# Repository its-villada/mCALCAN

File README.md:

# mCALCAN
Satélite CANSAT del instituto técnico salesiano Villada. 
Este desarrollo responde a la iniciativa conjunta entre la Comisión Nacional de Actividades Espaciales (CONAE) y el Ministerio de Ciencia, Tecnología e Innovación (MinCyT) tiene como objetivo principal acercar la
ciencia y la tecnología a jóvenes en edad escolar, mediante la participación en la Convocatoria CANSAT Argentina.

## Objetivos
### Misión Primaria
Consiste en el sensado de presión y temperatura y la transmisión de esos datos a la estación terrena,al menos una vez por segundo. Mediante estos dos parámetros calcularemos la altitud, ya que tanto presión como temperatura varían con la altitud.
Para el cálculo de la altura, nuestro CANSAT transmitirá los datos de temperatura y presión antes del despegue y de esa manera obtener los datos iniciales necesarios para el cálculo.
### Misión Secundaria
Aprovechando y como complemento de la misión primaria, la misión secundaria consiste en medir la atmósfera y sus condiciones, con el objetivo de armar un perfil de atmósfera que pueda ser implementado, más adelante, como parte del modelo meteorológico internacional para la generación de pronósticos o la calibración de radares meteorológicos. Esto significa, que se medirán parámetros ambientales de presión y temperatura (tomados en la misión primaria), a los que agregaremos
humedad relativa y porcentaje de CO2. Estos parámetros son medidos y correlacionados con las coordenadas (latitud, longitud y altitud) obtenidas por un módulo GPS.

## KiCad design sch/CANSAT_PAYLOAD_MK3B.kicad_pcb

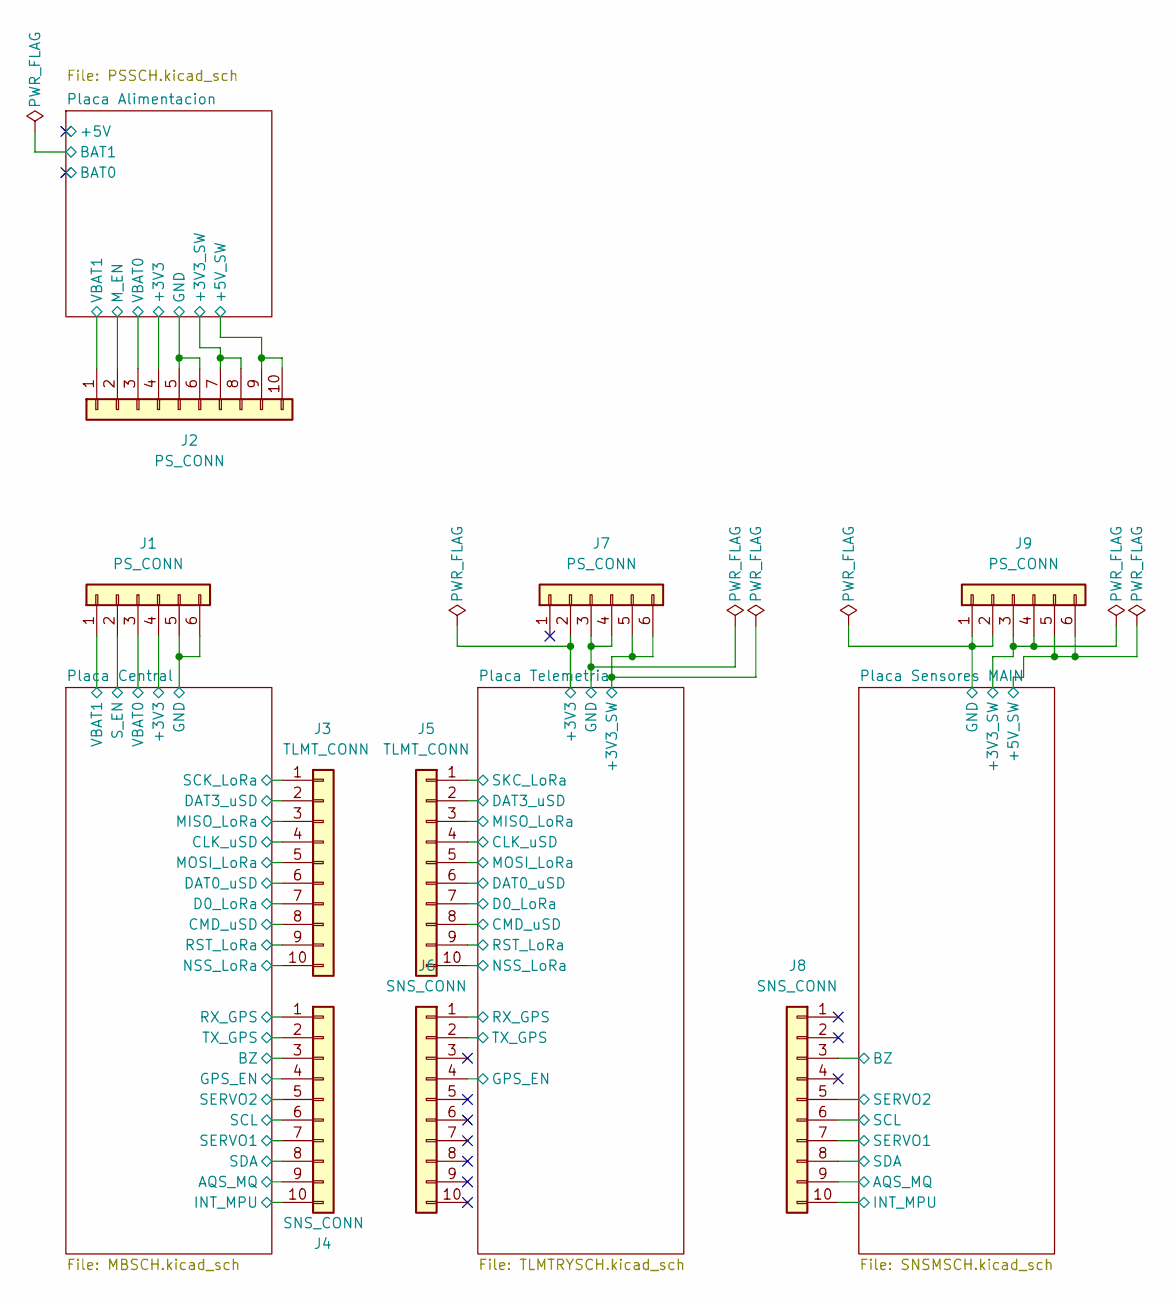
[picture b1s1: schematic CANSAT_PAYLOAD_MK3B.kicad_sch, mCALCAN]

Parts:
J1, J7, J9: PS_CONN; PCB_CONN_S
J2: PS_CONN; PCB_CONN
J3, J5: TLMT_CONN; PCB_CONN
J4, J6, J8: SNS_CONN; PCB_CONN

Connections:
/Placa Alimentacion/+3V3: J2.4; also elsewhere on the board
/Placa Alimentacion/+3V3_SW: J2.7, J2.8; also elsewhere on the board
/Placa Alimentacion/+5V_SW: J2.9, J2.10; also elsewhere on the board
/Placa Alimentacion/GND: J2.5, J2.6; also elsewhere on the board
/Placa Alimentacion/M_EN: J2.2; also elsewhere on the board
/Placa Alimentacion/VBAT0: J2.3; also elsewhere on the board
/Placa Alimentacion/VBAT1: J2.1; also elsewhere on the board
/Placa Central/+3V3: J1.4; also elsewhere on the board
/Placa Central/AQS_MQ: J4.9; also elsewhere on the board
/Placa Central/BZ: J4.3; also elsewhere on the board
/Placa Central/CLK_uSD: J3.4; also elsewhere on the board
/Placa Central/CMD_uSD: J3.8; also elsewhere on the board
/Placa Central/D0_LoRa: J3.7; also elsewhere on the board
/Placa Central/DAT0_uSD: J3.6; also elsewhere on the board
/Placa Central/DAT3_uSD: J3.2; also elsewhere on the board
/Placa Central/GND: J1.5, J1.6; also elsewhere on the board
/Placa Central/GPS_EN: J4.4; also elsewhere on the board
/Placa Central/INT_MPU: J4.10; also elsewhere on the board
/Placa Central/MISO_LoRa: J3.3; also elsewhere on the board
/Placa Central/MOSI_LoRa: J3.5; also elsewhere on the board
/Placa Central/NSS_LoRa: J3.10; also elsewhere on the board
/Placa Central/RST_LoRa: J3.9; also elsewhere on the board
/Placa Central/RX_GPS: J4.1; also elsewhere on the board
/Placa Central/SCK_LoRa: J3.1; also elsewhere on the board
/Placa Central/SCL: J4.6; also elsewhere on the board
/Placa Central/SDA: J4.8; also elsewhere on the board
/Placa Central/SERVO1: J4.7; also elsewhere on the board
/Placa Central/SERVO2: J4.5; also elsewhere on the board
/Placa Central/S_EN: J1.2; also elsewhere on the board
/Placa Central/TX_GPS: J4.2; also elsewhere on the board
/Placa Central/VBAT0: J1.3; also elsewhere on the board
/Placa Central/VBAT1: J1.1; also elsewhere on the board
/Placa Sensores MAIN/+3V3_SW: J9.3, J9.4; also elsewhere on the board
/Placa Sensores MAIN/+5V_SW: J9.5, J9.6; also elsewhere on the board
/Placa Sensores MAIN/AQS_MQ: J8.9; also elsewhere on the board
/Placa Sensores MAIN/BZ: J8.3; also elsewhere on the board
/Placa Sensores MAIN/GND: J9.1, J9.2; also elsewhere on the board
/Placa Sensores MAIN/INT_MPU: J8.10; also elsewhere on the board
/Placa Sensores MAIN/SCL: J8.6; also elsewhere on the board
/Placa Sensores MAIN/SDA: J8.8; also elsewhere on the board
/Placa Sensores MAIN/SERVO1: J8.7; also elsewhere on the board
/Placa Sensores MAIN/SERVO2: J8.5; also elsewhere on the board
/Placa Telemetria/+3V3: J7.2; also elsewhere on the board
/Placa Telemetria/+3V3_SW: J7.5, J7.6; also elsewhere on the board
/Placa Telemetria/CLK_uSD: J5.4; also elsewhere on the board
/Placa Telemetria/CMD_uSD: J5.8; also elsewhere on the board
/Placa Telemetria/D0_LoRa: J5.7; also elsewhere on the board
/Placa Telemetria/DAT0_uSD: J5.6; also elsewhere on the board
/Placa Telemetria/DAT3_uSD: J5.2; also elsewhere on the board
/Placa Telemetria/GND: J7.3, J7.4; also elsewhere on the board
/Placa Telemetria/GPS_EN: J6.4; also elsewhere on the board
/Placa Telemetria/MISO_LoRa: J5.3; also elsewhere on the board
/Placa Telemetria/MOSI_LoRa: J5.5; also elsewhere on the board
/Placa Telemetria/NSS_LoRa: J5.10; also elsewhere on the board
/Placa Telemetria/RST_LoRa: J5.9; also elsewhere on the board
/Placa Telemetria/RX_GPS: J6.1; also elsewhere on the board
/Placa Telemetria/SKC_LoRa: J5.1; also elsewhere on the board
/Placa Telemetria/TX_GPS: J6.2; also elsewhere on the board

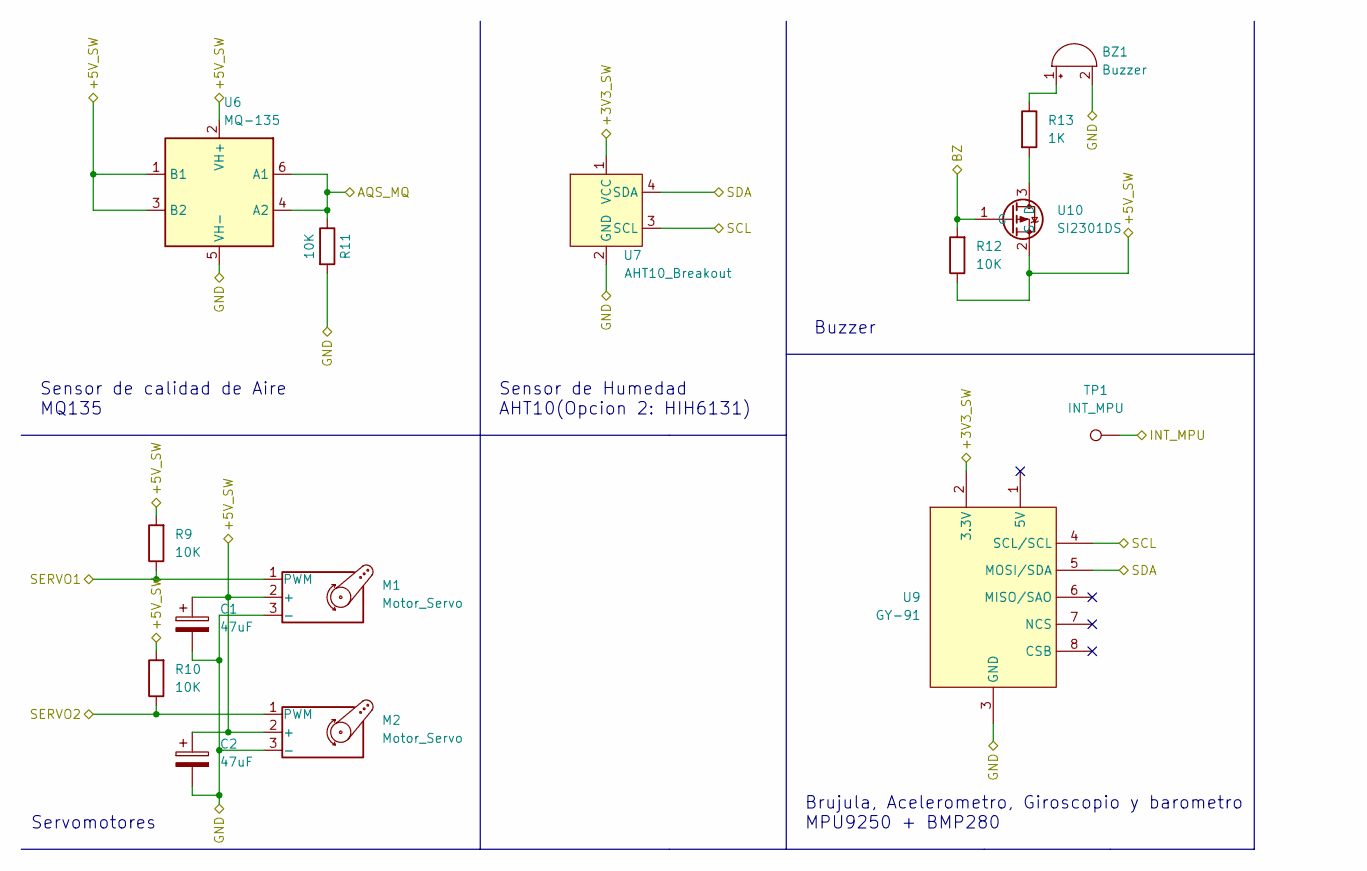
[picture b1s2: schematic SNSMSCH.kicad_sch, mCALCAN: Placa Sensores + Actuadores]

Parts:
BZ1: Buzzer; Buzzer_12x9.5RM7.6
C1, C2: 47uF; CP_Elec_4x5.3
M1, M2: Motor_Servo; PinHeader_1x03_P2.54mm_Vertical
R9, R10, R11, R12: 10K; R_0805_2012Metric_Pad1.20x1.40mm_HandSolder
R13: 1K; R_0805_2012Metric_Pad1.20x1.40mm_HandSolder
TP1: INT_MPU; TestPoint_THTPad_D1.5mm_Drill0.7mm
U6: MQ-135; MQ-6
U7: AHT10_Breakout
U9: GY-91; GY-91_Breakout
U10: SI2301DS; SOT-23

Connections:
/Placa Sensores MAIN/+3V3_SW: U7.1 (VCC), U9.2 (3.3V); also elsewhere on the board
/Placa Sensores MAIN/+5V_SW: C1.1, C2.1, M1.2 (+), M2.2 (+), R9.2, R10.2, R12.1, U6.1 (B1), U6.2 (VH+), U6.3 (B2), U10.2 (S); also elsewhere on the board
/Placa Sensores MAIN/AQS_MQ: R11.1, U6.4 (A2), U6.6 (A1); also elsewhere on the board
/Placa Sensores MAIN/BZ: R12.2, U10.1 (G); also elsewhere on the board
/Placa Sensores MAIN/GND: BZ1.2 (+), C1.2, C2.2, M1.3 (-), M2.3 (-), R11.2, U6.5 (VH-), U7.2 (GND), U9.3 (GND); also elsewhere on the board
/Placa Sensores MAIN/INT_MPU: TP1.1; also elsewhere on the board
/Placa Sensores MAIN/SCL: U7.3 (SCL), U9.4 (SCL/SCL); also elsewhere on the board
/Placa Sensores MAIN/SDA: U7.4 (SDA), U9.5 (MOSI/SDA); also elsewhere on the board
/Placa Sensores MAIN/SERVO1: M1.1 (PWM), R9.1; also elsewhere on the board
/Placa Sensores MAIN/SERVO2: M2.1 (PWM), R10.1; also elsewhere on the board
unnamed: BZ1.1 (-), R13.1
unnamed: R13.2, U10.3 (D)

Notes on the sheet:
Buzzer
Sensor de Humedad AHT10(Opcion 2: HIH6131)
Brujula, Acelerometro, Giroscopio y barometro MPU9250 + BMP280
Sensor de calidad de Aire MQ135
Servomotores

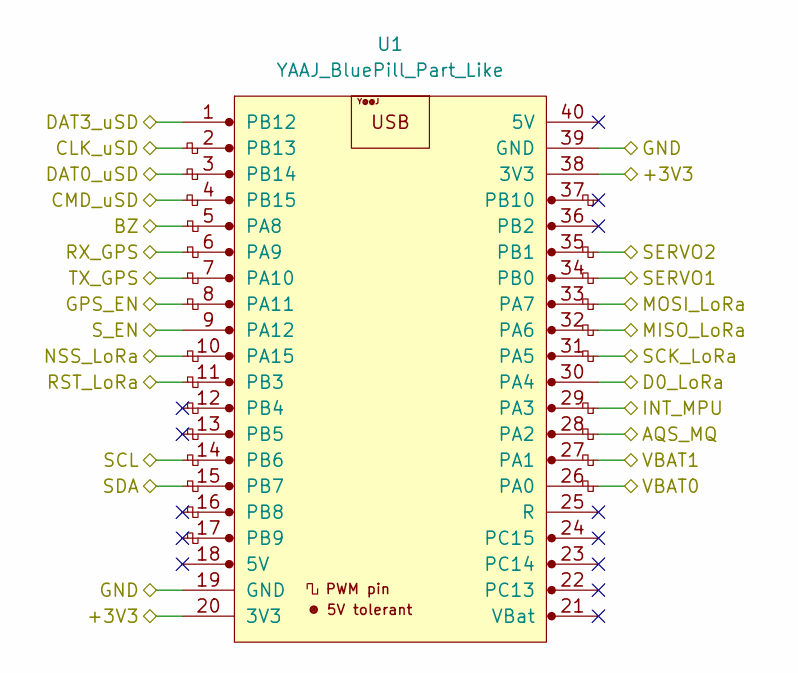
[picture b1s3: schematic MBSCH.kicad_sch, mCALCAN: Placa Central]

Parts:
U1: YAAJ_BluePill_Part_Like; YAAJ_BluePill_2

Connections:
/Placa Central/+3V3: U1.20 (3V3), U1.38 (3V3); also elsewhere on the board
/Placa Central/AQS_MQ: U1.28 (PA2); also elsewhere on the board
/Placa Central/BZ: U1.5 (PA8); also elsewhere on the board
/Placa Central/CLK_uSD: U1.2 (PB13); also elsewhere on the board
/Placa Central/CMD_uSD: U1.4 (PB15); also elsewhere on the board
/Placa Central/D0_LoRa: U1.30 (PA4); also elsewhere on the board
/Placa Central/DAT0_uSD: U1.3 (PB14); also elsewhere on the board
/Placa Central/DAT3_uSD: U1.1 (PB12); also elsewhere on the board
/Placa Central/GND: U1.19 (GND), U1.39 (GND); also elsewhere on the board
/Placa Central/GPS_EN: U1.8 (PA11); also elsewhere on the board
/Placa Central/INT_MPU: U1.29 (PA3); also elsewhere on the board
/Placa Central/MISO_LoRa: U1.32 (PA6); also elsewhere on the board
/Placa Central/MOSI_LoRa: U1.33 (PA7); also elsewhere on the board
/Placa Central/NSS_LoRa: U1.10 (PA15); also elsewhere on the board
/Placa Central/RST_LoRa: U1.11 (PB3); also elsewhere on the board
/Placa Central/RX_GPS: U1.6 (PA9); also elsewhere on the board
/Placa Central/SCK_LoRa: U1.31 (PA5); also elsewhere on the board
/Placa Central/SCL: U1.14 (PB6); also elsewhere on the board
/Placa Central/SDA: U1.15 (PB7); also elsewhere on the board
/Placa Central/SERVO1: U1.34 (PB0); also elsewhere on the board
/Placa Central/SERVO2: U1.35 (PB1); also elsewhere on the board
/Placa Central/S_EN: U1.9 (PA12); also elsewhere on the board
/Placa Central/TX_GPS: U1.7 (PA10); also elsewhere on the board
/Placa Central/VBAT0: U1.26 (PA0); also elsewhere on the board
/Placa Central/VBAT1: U1.27 (PA1); also elsewhere on the board

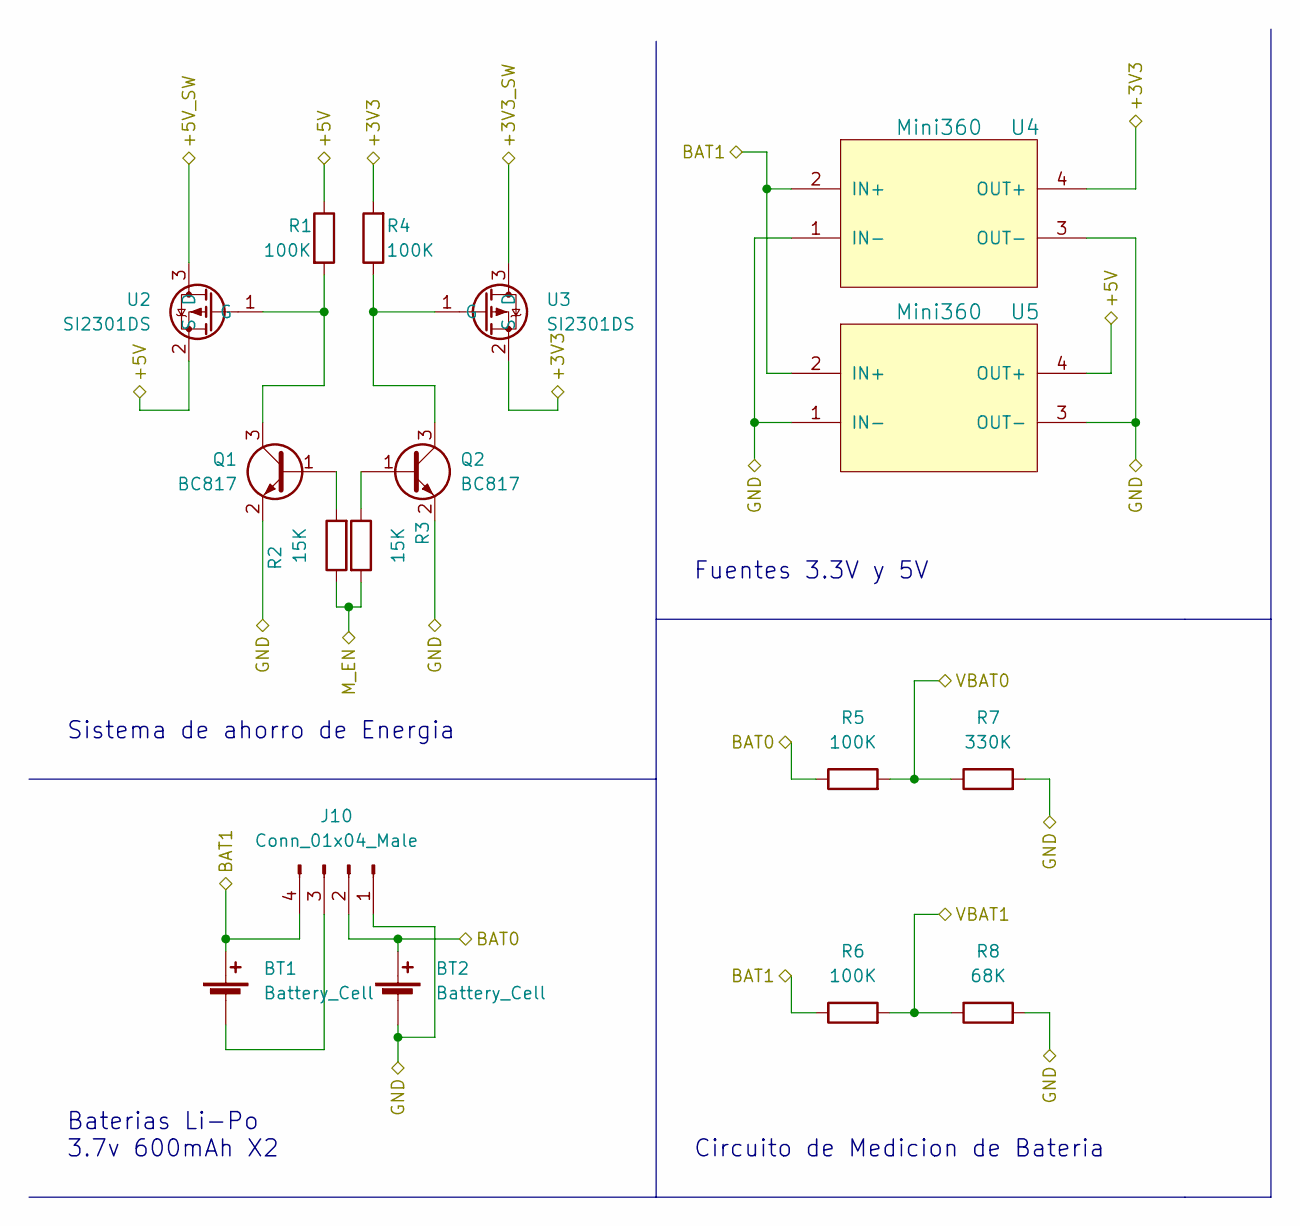
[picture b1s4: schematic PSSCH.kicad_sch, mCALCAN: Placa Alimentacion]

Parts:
BT1, BT2: Battery_Cell; Molex_Micro-Latch_53253-0270_1x02_P2.00mm_Vertical
J10: Conn_01x04_Male; PinHeader_1x04_P2.54mm_Vertical
Q1, Q2: BC817; SOT-23
R1, R4, R5, R6: 100K; R_0805_2012Metric_Pad1.20x1.40mm_HandSolder
R2, R3: 15K; R_0805_2012Metric_Pad1.20x1.40mm_HandSolder
R7: 330K; R_0805_2012Metric_Pad1.20x1.40mm_HandSolder
R8: 68K; R_0805_2012Metric_Pad1.20x1.40mm_HandSolder
U2, U3: SI2301DS; SOT-23
U4, U5: Mini360; Mini360_step-down

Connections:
/Placa Alimentacion/+3V3: R4.2, U3.2 (S), U4.4 (OUT+); also elsewhere on the board
/Placa Alimentacion/+3V3_SW: U3.3 (D); also elsewhere on the board
/Placa Alimentacion/+5V: R1.1, U2.2 (S), U5.4 (OUT+)
/Placa Alimentacion/+5V_SW: U2.3 (D); also elsewhere on the board
/Placa Alimentacion/BAT0: BT2.1 (+), J10.2, R5.1
/Placa Alimentacion/BAT1: BT1.1 (+), J10.4, R6.1, U4.2 (IN+), U5.2 (IN+)
/Placa Alimentacion/GND: BT2.2 (-), J10.1, Q1.2 (E), Q2.2 (E), R7.2, R8.2, U4.1 (IN-), U4.3 (OUT-), U5.1 (IN-), U5.3 (OUT-); also elsewhere on the board
/Placa Alimentacion/M_EN: R2.1, R3.2; also elsewhere on the board
/Placa Alimentacion/VBAT0: R5.2, R7.1; also elsewhere on the board
/Placa Alimentacion/VBAT1: R6.2, R8.1; also elsewhere on the board
unnamed: BT1.2 (-), J10.3
unnamed: Q1.1 (B), R2.2
unnamed: Q1.3 (C), R1.2, U2.1 (G)
unnamed: Q2.1 (B), R3.1
unnamed: Q2.3 (C), R4.1, U3.1 (G)

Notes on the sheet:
Baterias Li-Po 3.7v 600mAh X2
Sistema de ahorro de Energia
Fuentes 3.3V y 5V
Circuito de Medicion de Bateria

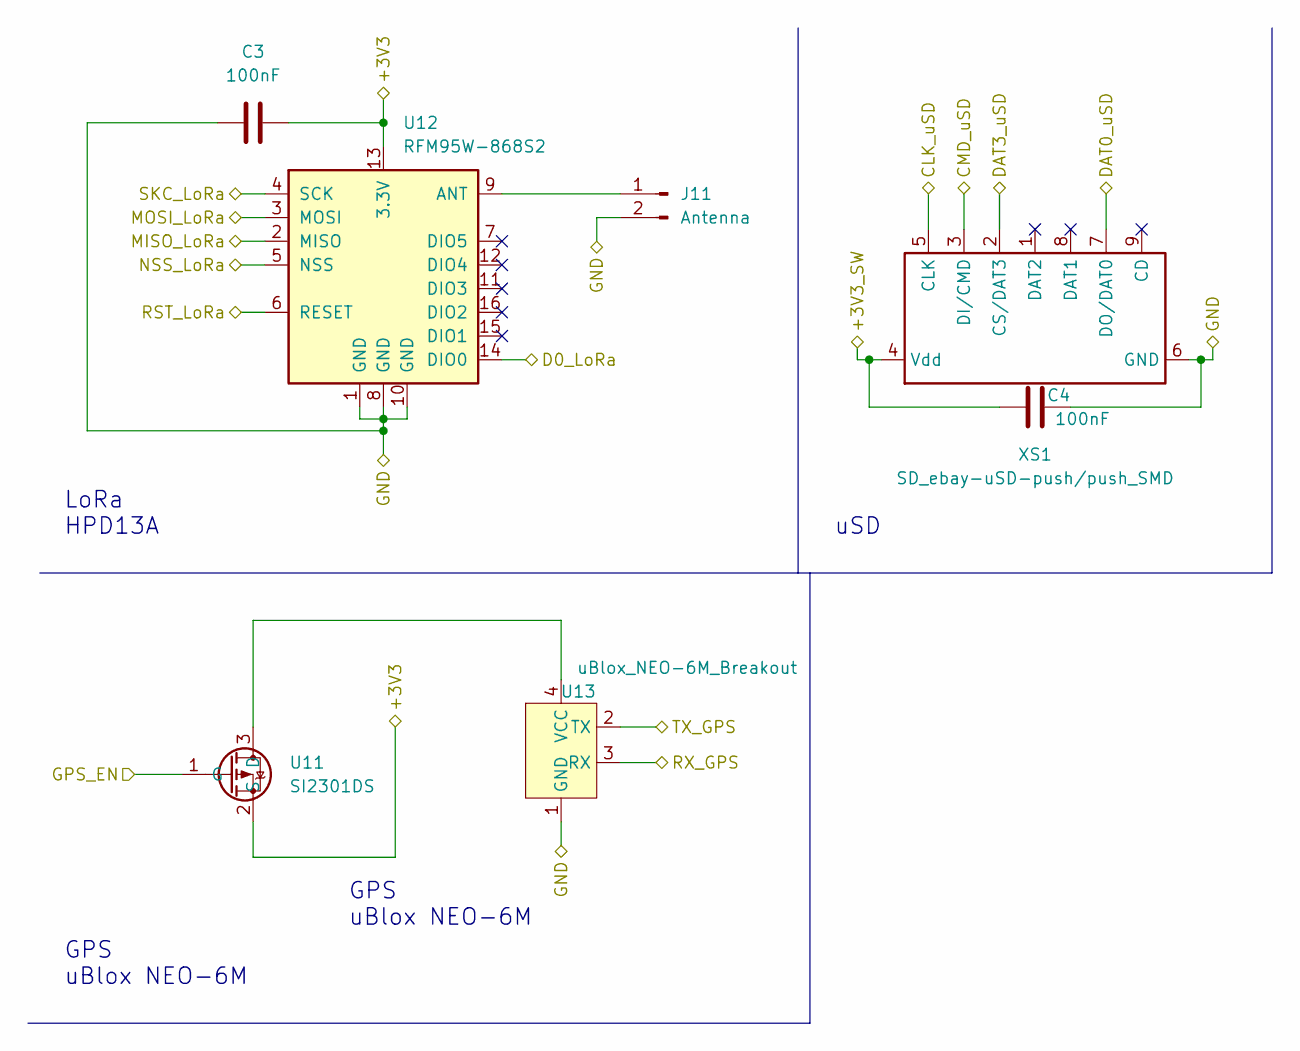
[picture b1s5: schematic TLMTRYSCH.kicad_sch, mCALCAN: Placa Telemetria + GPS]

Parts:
C3, C4: 100nF; C_0805_2012Metric_Pad1.18x1.45mm_HandSolder
J11: Antenna; U.FL_Molex_MCRF_73412-0110_Vertical
U11: SI2301DS; SOT-23
U12: RFM95W-868S2; HOPERF_RFM9XW_SMD
U13: uBlox_NEO-6M_Breakout; uBlox-NEO-6M_Breakout
XS1: SD_ebay-uSD-push/push_SMD; Conn_uSDcard

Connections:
/Placa Telemetria/+3V3: C3.2, U11.2 (S), U12.13 (3.3V); also elsewhere on the board
/Placa Telemetria/+3V3_SW: C4.1, XS1.4 (Vdd); also elsewhere on the board
/Placa Telemetria/CLK_uSD: XS1.5 (CLK); also elsewhere on the board
/Placa Telemetria/CMD_uSD: XS1.3 (DI/CMD); also elsewhere on the board
/Placa Telemetria/D0_LoRa: U12.14 (DIO0); also elsewhere on the board
/Placa Telemetria/DAT0_uSD: XS1.7 (DO/DAT0); also elsewhere on the board
/Placa Telemetria/DAT3_uSD: XS1.2 (CS/DAT3); also elsewhere on the board
/Placa Telemetria/GND: C3.1, C4.2, J11.2, U12.1 (GND), U12.8 (GND), U12.10 (GND), U13.1 (GND), XS1.6 (GND); also elsewhere on the board
/Placa Telemetria/GPS_EN: U11.1 (G); also elsewhere on the board
/Placa Telemetria/MISO_LoRa: U12.2 (MISO); also elsewhere on the board
/Placa Telemetria/MOSI_LoRa: U12.3 (MOSI); also elsewhere on the board
/Placa Telemetria/NSS_LoRa: U12.5 (NSS); also elsewhere on the board
/Placa Telemetria/RST_LoRa: U12.6 (RESET); also elsewhere on the board
/Placa Telemetria/RX_GPS: U13.3 (RX); also elsewhere on the board
/Placa Telemetria/SKC_LoRa: U12.4 (SCK); also elsewhere on the board
/Placa Telemetria/TX_GPS: U13.2 (TX); also elsewhere on the board
unnamed: J11.1, U12.9 (ANT)
unnamed: U11.3 (D), U13.4 (VCC)

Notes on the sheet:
GPS uBlox NEO-6M
LoRa HPD13A
uSD

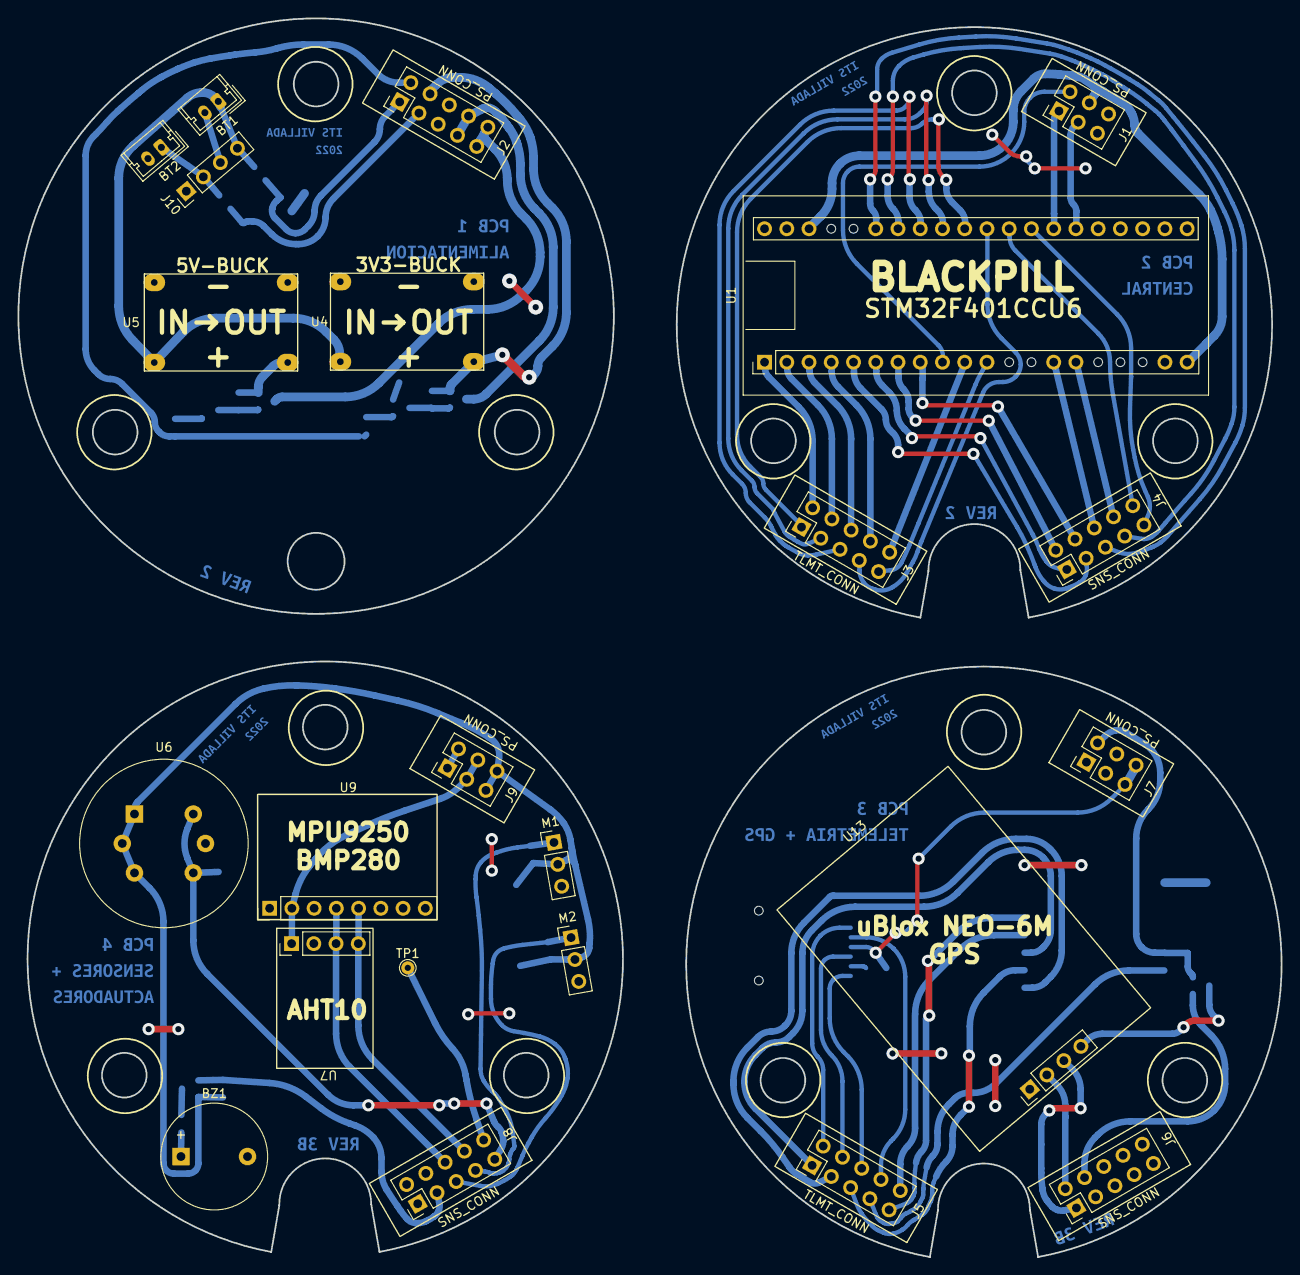
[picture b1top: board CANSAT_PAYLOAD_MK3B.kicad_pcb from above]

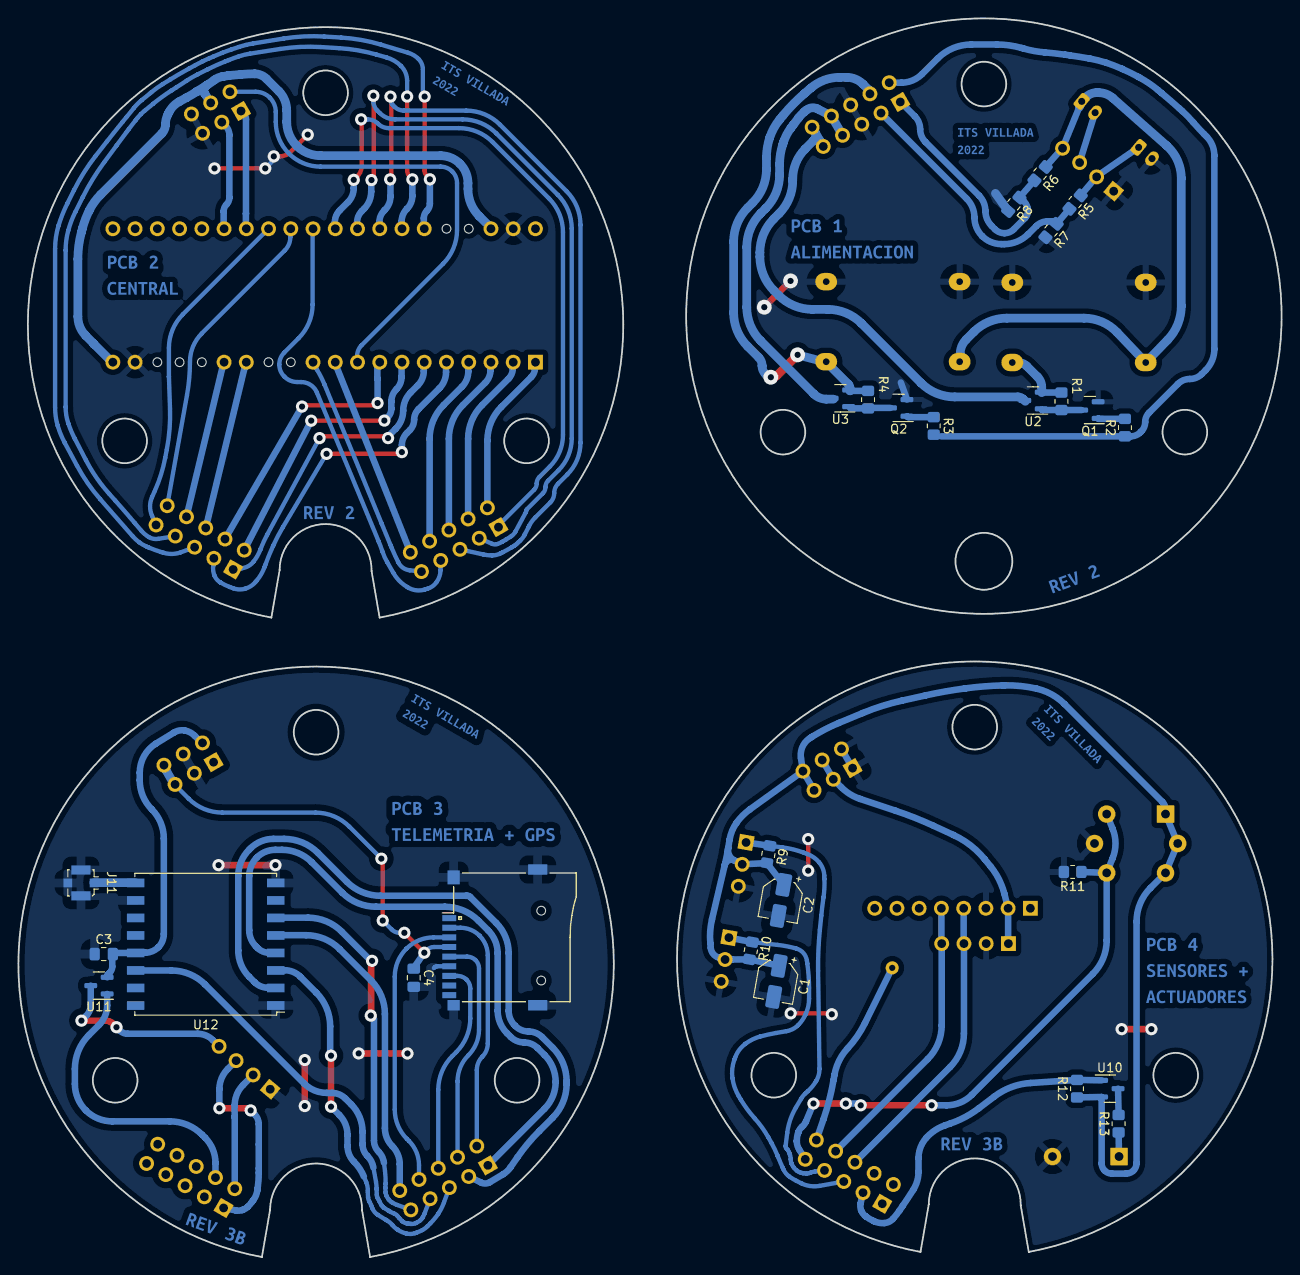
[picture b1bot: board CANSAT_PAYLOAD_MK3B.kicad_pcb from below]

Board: 2 copper layers, 144.3 x 141.5 mm, 61 parts (38 on the bottom side), 70 nets.

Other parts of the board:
kibuzzard-6319D247, kibuzzard-6319D247#2, kibuzzard-6319D247#3, kibuzzard-6319D247#4: G***; kibuzzard-6319D247
kibuzzard-6344A53A: G***; kibuzzard-6344A53A
kibuzzard-63173E9C: G***; kibuzzard-63173E9C
kibuzzard-63173EF4: G***; kibuzzard-63173EF4
kibuzzard-63447E72, kibuzzard-63447E72#2: G***; kibuzzard-63447E72
kibuzzard-63447E86: G***; kibuzzard-63447E86
kibuzzard-634739A2: G***; kibuzzard-634739A2
kibuzzard-634739B3: G***; kibuzzard-634739B3

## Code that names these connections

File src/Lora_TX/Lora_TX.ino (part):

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#define LORA_SPREAD_FACTOR 7     // Spreading factor, defaults to 7. Supported values are between 6 and 12 (En Argentina se puede utilizar entre 7 a 10)
#define LORA_SIG_BANDWIDTH 125E3 // Signal bandwidth in Hz, defaults to 125E3. Supported values are 7.8E3, 10.4E3, 15. 6E3, 20.8E3, 31.25E3, 41.7E3, 62.5E3, 125E3, 250E3, and 500E3
#define LORA_CODING_RATE 5       // Denominator of the coding rate, defaults to 5. Supported values are between 5 and 8, these correspond to coding rates of 4/5 and 4/8. The coding rate numerator is fixed at 4.
#define RST PB3                  // Pin Reset del transciver LoRa
#define IRQ PA4                  // Pin DIO0 del transciver LoRa
#define NSS PA15                 // Pin CS del transciver LoRa
#define INTMPU PA3               // Pin de interrupcion del MPU6050
#define gpsOn PA11               // Pin de activacion del GPS
#define BAT0 PA0                 // Pin de tension de bateria 1
#define BAT1 PA1                 // Pin de tension de bateria 2
#define MainS PA12               // Pin Sensors enable
#define AQS PA2                  // Pin del sensor MQ-135
#define buzzer PA8               // Pin del buzzer de recuperacion
#define servoDerPin PB1          // Pin del servo derecha
#define servoIzqPin PB0          // Pin del servo izquierda
#define HW_TIMER_INTERVAL_MS 1
#define TIMER_INTERVAL_1 6L   // Intervalo1 salta cada 6 ms
#define TIMER_INTERVAL_2 500L // Intervalo2 salta cada 500 ms
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    pinMode(MainS, OUTPUT);
    pinMode(gpsOn, OUTPUT);             // FUNCIONA EN LOGICA INVERSA!
    pinMode(buzzer, OUTPUT_OPEN_DRAIN); // FUNCIONA EN LOGICA INVERSA!
    pinMode(BAT0, INPUT);
    pinMode(BAT1, INPUT);
    pinMode(INTMPU, INPUT);
    pinMode(AQS, INPUT);
    digitalWrite(LED_BUILTIN, HIGH);
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
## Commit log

2022-08-03 add documents
2022-08-06 initial updates
2022-08-08 integración con estación terrena
2022-08-08 read data
2022-08-12 Update Lora_TX.ino
    Es el codigo para empezar la mision secundaria
2022-08-24 Update Lora_TX.ino
    Le agrego el sensor de calidad de aire
2022-08-24 Update Lora_RX.ino
    Ya le cambie los valores a las variables booleanas, y le agrego el sensor de calidad de aire
2022-08-24 Update Lora_TX.ino
    Agrego la parte del aht10
2022-08-25 protocolo
2022-08-25 Update Lora_TX.ino
    Tried to optimize code
2022-08-28 Update Lora_TX.ino
    Reducido un poco el tamaño del programa (95% a 86%)
    Repetitividad reducida con el uso de funciones
    Codigo acomodado
    Prototipos agregados
    Ahora se usa un puerto SPI fisico para la MicroSD (antes era por software)
    Ahora funciona la telemetria local en MicroSD
2022-08-28 Add files via upload
    Librerias usadas en esta rama con sus respectivas modificaciones
2022-08-28 Delete arduino-LoRa-STM32-master.zip
    Libreria en desuso reemplazada por la estandard de arduino
2022-08-28 Update Lora_TX.ino
    Optimizado aun mas el uso de la memoria estatica (86 a 84%)
    Ahora no abrimos y cerramos el mismo archivo por cada linea que escribimos. Una vez abierto, usamos File.flush() para pasar todo a la MicroSD y liberar memoria dinamica
    Los tiempos de escritura tienen una falla periodica que duplica su tiempo de escritura
    Cambiamos la libreria SDFat por la libreria estandard de arduino SD (mas liviana, menos compleja)
2022-08-29 Codigo provisional Flyback
    Código provisional del flyback, sin control de servos
2022-08-31 actualizado codigo flyback
2022-09-01 ejemplo
2022-09-02 optimized flyback code
    Para optimizar el uso de recursos se cambio el protocolo del GPS de NMEA a UBX y se usa una librería mas ligera.
2022-09-06 Updated fly-back code
    Se añado el control de servos al código de prueba de flyback y se realizaron cambios de optimización
2022-09-06 Carpetas nuevas
    Agregada carpeta con las librerias utilizadas y carpeta con recursos extras para la configuracion del cansat (GPS y compas)
2022-09-14 new extra codes for testing
2022-09-14 libraries updates
    cambios en las librerias: Se elimino la libreria ServoTiemr2 y se actualizo CustomQMC5883L
2022-09-15 Update Lora_TX.ino
    Es un codigo con algunas funciones eliminadas para la muestra de expotronica. No debe ser merged al main branch.
2022-09-18 Add files via upload
    Cambio para usar SPI2
2022-09-21 UBX -> NMEA
    cambiado el protocolo del gps a nmea
2022-09-21 added suport for softwareserial bridge
2022-09-22 borrado de archivos redundantes
2022-09-22 borrado de librerías no utilizadas
2022-09-22 borrado de librerías redundantes
2022-09-22 uploaded 3d print models
2023-11-23 Agrega fuente de los esquemáticos y diseños de pcb
